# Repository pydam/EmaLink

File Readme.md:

# EmaLink

A device that bridges the communication between Loop software application and Omnipod and Medtronic insulin pumps. This is a fork from RileyLink, focusing on reducing size of the device, improving communication range and extending battery life. Also, you can charge EmaLink with any micro USB charger - much broader available vs. the mini port USB used by RileyLink.

### Turning on
Use a nail, a small plastic or a wood bit to move the power switch towards the USB port. When EmaLink is powered on, you should see a red and a green LED turning on for 1 second.

### Connecting EmaLink to Loop/FreeAPS/AndroidAPS
Please follow the instructions provided by each application for connecting to EmaLink, the procedure is the same as for RileyLink, just the name of the device will be EmaLink.Once EmaLink is connected to Loop/FreeAPS/AndroidAPS, a green led will start blinking every 3 seconds on EmaLink.

### Charging

Once the battery gets almost depleted, a red led will start blinking every 3 seconds.
To charge it, you can use any micro USB charger from a phone, tablet, headset or another device. You can even use a power bank to charge it if it has a micro USB cable. Charging is considered finished after the red led (the one close to the USB connector) is turned off. It may take up to 3 hours for Nano.
For QI versions, charging can be also done with any QI compatible charge. Place EmaLink with the coil (you can see a round, copper coil, through the case) down on the middle of the QI charger and check that a red led is lighting from the top of the EmaLink. Once charging is completed, you should remove EmaLink from the charger as the charger reduces communication range.
Charging can be done every few days until EmaLink is fully charged (the red led turned off) or for a few minutes every day, depending on your schedule. Overnight charging also works well with a Micro USB charge but avoid leaving QI versions on the QI charger overnight as this reduced communication range and may generate red loops.

### LED Lights 

There are 3 leds on the back of the device: a red one, close to the micro USB charging port, and a red + green cluster on the other side. First, turn the EmaLink on by flipping the switch located next to the micro USB port. After you switch-on EmaLink, the red + green cluster will light-up for 1 second. When you connect EmaLink to AAPS on Loop over bluetooth, the green led will start blinking every 3 seconds. The green led will stop blinking once battery is almost depleted. The red led will start blinking once battery is almost depleted, you should consider charging it in the next few hours.

### Case

I have designed a new case to be 3D printed with TPU material. TPU is a flexbile material that cannot be shattered, this makes EmaLink
drop proof. There are several case styles to chose from, pick the one that makes most sense for your needs.

### Hardware

See the [hardware](https://github.com/sks01/emalink/tree/master/hardware) directory for design files to build it. The hardware design is released under [Creative Commons Share-alike 3.0](http://creativecommons.org/licenses/by-sa/3.0/).  

### Firmware

The code in the [firmware](https://github.com/sks01/emalink/tree/master/firmware) directory runs on the hardware.  There are two main chips and thus two firmware images.
Check the "EmaLink 3_7 3_8 - firmware update guide.docx" if you would like to understand how you can update the firmware for EmaLink with PCB version 3.7, 3.8 or 3.9.

Check the "EmaLink 3_2 3_3 - firmware update guide.docx" if you would like to understand how you can update the firmware for EmaLink with PCB version 3.2 or 3.3. You can use breadboard wires also but you may need to keep them at an angle while flashing as the PCB holes are slightly bigger.

Check the "EmaLink%204_4%20-%20firmware%20update%20guide.pdf" if you would like to understand how you can update the firmware for EmaLink with PCB version 4.x. 

### License

The MIT License (MIT)

Copyright (c) 2015 Pete Schwamb

Permission is hereby granted, free of charge, to any person obtaining a copy
of this software and associated documentation files (the "Software"), to deal
in the Software without restriction, including without limitation the rights
to use, copy, modify, merge, publish, distribute, sublicense, and/or sell
copies of the Software, and to permit persons to whom the Software is
furnished to do so, subject to the following conditions:

The above copyright notice and this permission notice shall be included in all
copies or substantial portions of the Software.

THE SOFTWARE IS PROVIDED "AS IS", WITHOUT WARRANTY OF ANY KIND, EXPRESS OR
IMPLIED, INCLUDING BUT NOT LIMITED TO THE WARRANTIES OF MERCHANTABILITY,
FITNESS FOR A PARTICULAR PURPOSE AND NONINFRINGEMENT. IN NO EVENT SHALL THE
AUTHORS OR COPYRIGHT HOLDERS BE LIABLE FOR ANY CLAIM, DAMAGES OR OTHER
LIABILITY, WHETHER IN AN ACTION OF CONTRACT, TORT OR OTHERWISE, ARISING FROM,
OUT OF OR IN CONNECTION WITH THE SOFTWARE OR THE USE OR OTHER DEALINGS IN THE
SOFTWARE.

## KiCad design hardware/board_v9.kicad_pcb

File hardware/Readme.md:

# EmaLink Hardware

 *  Project_EL v4.3_2021-04-12_19-27-16.zip - EasyEDA project for version 4.3
 *  Schematic_EL v4.x.pdf - Schematic for versions 4.1-4.2
 *  Project_EL v4.1.zip - EasyEDA project for versions 4.1-4.2
 *  Gerber_EL v4.2 PCB.zip - Gerber files for version 4.2
 
### PCB Assembly

You will have to look at the schematic and the board design in Kicad to know where the parts go, and how they are oriented.

I use a hot-air rework station to solder the BLE113 module, the CC1110 chip, the USB connector, the 24Mhz crystal and the 3 power coils. The rest can be soldered with normal soldering station but require good soldering skills (especially the balun and the RF tuning network)

### License

The hardware design is released under [Creative Commons Share-alike 3.0](http://creativecommons.org/licenses/by-sa/3.0/).

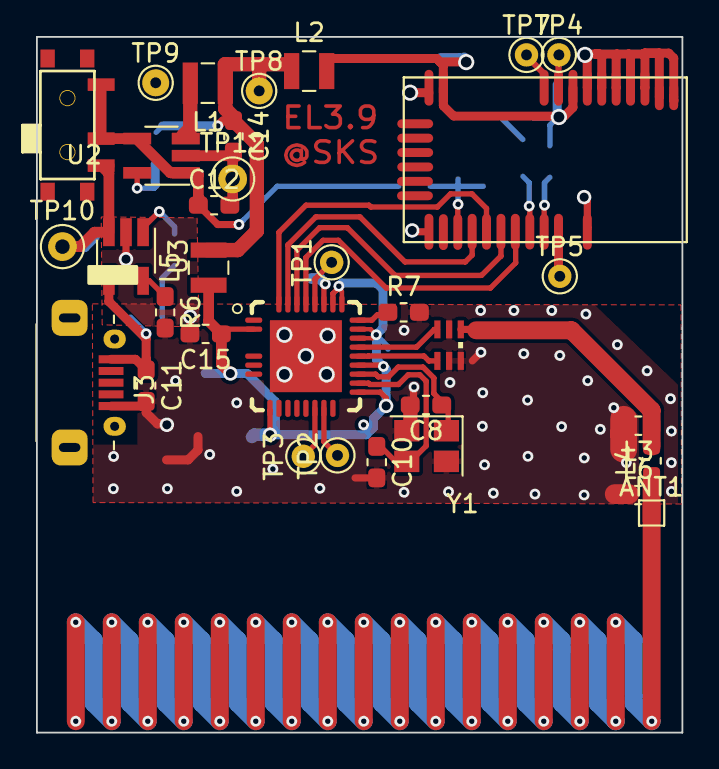
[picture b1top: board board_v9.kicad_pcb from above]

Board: 2 copper layers, 35.9 x 38.6 mm, 52 parts (0 on the bottom side), 34 nets.

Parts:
ANT1: ANTENNA; TestPoint_Pad_1.0x1.0mm
C1, C2, C5, C6, C9, C15, C16: 1uF; C_0603_1608Metric_Pad1.05x0.95mm_HandSolder
C3, C4, C12, C14: 10uF; C_0603_1608Metric_Pad1.05x0.95mm_HandSolder
C7, C11, C13: 4.7uF; C_0603_1608Metric_Pad1.05x0.95mm_HandSolder
C8, C10: 12pF ±5%; C_0603_1608Metric_Pad1.05x0.95mm_HandSolder
CC1: CC1110; QLP-36_CC1110
D3: ORANGE; LED_0603_1608Metric_Pad1.05x0.95mm_HandSolder
D4: RED; LED_0603_1608Metric_Pad1.05x0.95mm_HandSolder
D5: GREEN; LED_0603_1608Metric_Pad1.05x0.95mm_HandSolder
IC1: 0433BM15A0001
J3: USB_B_Micro; U254-051T-4BH23-S2B
L1, L2, L5: 1.5u uH; L_Wuerth_MAPI-2512
L3: 6.8nH; L_0603_1608Metric
L4, L6: 12nH; L_0603_1608Metric
R5: 470; C_0603_1608Metric_Pad1.05x0.95mm_HandSolder
R6: 8.06k; C_0603_1608Metric_Pad1.05x0.95mm_HandSolder
R7: 56kOhm ± 1%; C_0603_1608Metric_Pad1.05x0.95mm_HandSolder
R8, R11: 249k; C_0603_1608Metric_Pad1.05x0.95mm_HandSolder
R9: 100; C_0603_1608Metric_Pad1.05x0.95mm_HandSolder
R12: 82k; C_0603_1608Metric_Pad1.05x0.95mm_HandSolder
R13: 100k; C_0603_1608Metric_Pad1.05x0.95mm_HandSolder
SW1: SW_SPDT; SLIDE_SWITCH_SMD
TP1: RES_CC; TestPoint_THTPad_D1.5mm_Drill0.7mm
TP2: DC_CC; TestPoint_THTPad_D1.5mm_Drill0.7mm
TP3: DD_CC; TestPoint_THTPad_D1.5mm_Drill0.7mm
TP4: DC_BLE; TestPoint_THTPad_D1.5mm_Drill0.6mm
TP5: RES_BLE; TestPoint_THTPad_D1.5mm_Drill0.6mm
TP7: DD_BLE; TestPoint_THTPad_D1.5mm_Drill0.6mm
TP8: VDD; TestPoint_THTPad_D1.5mm_Drill0.6mm
TP9: GND; TestPoint_THTPad_D1.5mm_Drill0.6mm
TP10: Vbat; TestPoint_THTPad_D2.0mm_Drill1.0mm
TP12: GND; TestPoint_THTPad_D2.0mm_Drill1.0mm
U1: BLE113-A
U2: XI AN Aerosemi M3406; SOT-23-5_HandSoldering
U3: XT4052; SOT-23-5_HandSoldering
Y1: 24Mhz; Crystal_SMD_3225-4Pin_3.2x2.5mm

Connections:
BLE_VBAT: C7.1, R11.1, R13.2, U1.P0_6
GND: C1.2, C2.2, C3.2, C4.2, C5.2, C6.2, C7.2, C8.2, C9.1, C10.2, C11.2, C12.2, C13.2, C14.2, C15.2, C16.2, CC1.37, IC1.2, IC1.5, IC1.6, J3.5, L3.2, L6.1, R6.2, R7.2, R12.1, R13.1, TP9.1, TP12.1, U1.GND, U1.GND@2, U1.GND@3, U1.GND@4, U1.GND@5, U1.GND@6, U1.GND@7, U1.GND@8, U1.GND@9, U1.GND@10, U2.2, U3.2, Y1.2, Y1.4
LED1_OUT: D5.2, U1.P0_0
LED2_OUT: R9.1, U1.P0_1
unnamed: ANT1.1, L4.1, L6.2
unnamed: C1.1, C2.1, C4.1, C6.1, C15.1, C16.1, CC1.2, CC1.10, CC1.19, CC1.22, CC1.25, CC1.26, CC1.28, CC1.29, L5.1
unnamed: C3.1, C5.1, D4.1, D5.1, L2.2, U1.AVDD, U1.DVDD
unnamed: C8.1, CC1.21, Y1.1
unnamed: C9.2, CC1.30
unnamed: C10.1, CC1.20, Y1.3
unnamed: CC1.15, TP3.1
unnamed: CC1.16, TP2.1
unnamed: CC1.23, IC1.4
unnamed: CC1.24, IC1.3
unnamed: CC1.27, R7.1
unnamed: CC1.31, TP1.1
unnamed: CC1.32, U1.P0_2
unnamed: CC1.33, U1.P0_3
unnamed: CC1.34, U1.P0_5
unnamed: CC1.35, U1.P0_4
unnamed: D3.2, R5.1
unnamed: D4.2, R9.2
unnamed: IC1.1, L3.1, L4.2
unnamed: L1.2, U2.3
unnamed: R5.2, U3.1
unnamed: R6.1, U3.5
unnamed: R8.1, R12.2, U2.5
unnamed: TP4.1, U1.P2_2
unnamed: TP5.1, U1.RESET
unnamed: TP7.1, U1.P2_1
USB_5V: C11.1, D3.1, J3.1, U3.4
V+: C12.1, R11.2, SW1.1, SW1.2, U2.1, U2.4
VBAT: C13.1, SW1.3, TP10.1, U3.3
VDD: C14.1, L1.1, L2.1, L5.2, R8.2, TP8.1

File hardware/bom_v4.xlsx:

Qty | Reference(s) | Value | Footprint
1 | ANT1 | ANTENNA | footprints:W3127 433Mhz
7 | C1, C2, C5, C6, C9, C15, C16 | 1uF | Capacitor_SMD:C_0603_1608Metric_Pad1.05x0.95mm_HandSolder
4 | C3, C4, C12, C14 | 10uF | Capacitor_SMD:C_0603_1608Metric_Pad1.05x0.95mm_HandSolder
3 | C7, C11, C13 | 4.7uF | Capacitor_SMD:C_0603_1608Metric_Pad1.05x0.95mm_HandSolder
2 | C8, C10 | 12pF | Capacitor_SMD:C_0603_1608Metric_Pad1.05x0.95mm_HandSolder
1 | CC1 | CC1110 | footprints:QLP-36_CC1110
1 | D3 | ORANGE | LED_SMD:LED_0603_1608Metric_Pad1.05x0.95mm_HandSolder
1 | D4 | RED | LED_SMD:LED_0603_1608Metric_Pad1.05x0.95mm_HandSolder
1 | D5 | GREEN | LED_SMD:LED_0603_1608Metric_Pad1.05x0.95mm_HandSolder
1 | IC1 | 0433BM15A0001 | footprints:0433BM15A0001
1 | J3 | USB_B_Micro | footprints:U254-051T-4BH23-S2B
3 | L1, L2, L5 | 1.5u uH | Inductor_SMD:L_Wuerth_MAPI-2512
1 | L3 | 6.8nH | Inductor_SMD:L_0402_1005Metric
1 | L4 | 12nH | Inductor_SMD:L_0402_1005Metric
1 | R5 | 470Ohm | Capacitor_SMD:C_0603_1608Metric_Pad1.05x0.95mm_HandSolder
1 | R6 | 8.06k | Capacitor_SMD:C_0603_1608Metric_Pad1.05x0.95mm_HandSolder
1 | R7 | 56kOhm | Capacitor_SMD:C_0603_1608Metric_Pad1.05x0.95mm_HandSolder
2 | R8, R11 | 249k | Capacitor_SMD:C_0603_1608Metric_Pad1.05x0.95mm_HandSolder
1 | R9 | 100Ohm | Capacitor_SMD:C_0603_1608Metric_Pad1.05x0.95mm_HandSolder
1 | R10 | 0Ohm | Capacitor_SMD:C_0603_1608Metric_Pad1.05x0.95mm_HandSolder
1 | R12 | 82k | Capacitor_SMD:C_0603_1608Metric_Pad1.05x0.95mm_HandSolder
1 | R13 | 100k | Capacitor_SMD:C_0603_1608Metric_Pad1.05x0.95mm_HandSolder
1 | SW1 | SW_SPDT | footprints:SLIDE_SWITCH_SMD
1 | U1 | BLE113-A | footprints:BLE113-A
1 | U2 | XI AN Aerosemi M3406 | Package_TO_SOT_SMD:SOT-23-5_HandSoldering
1 | U3 | XT4052 | Package_TO_SOT_SMD:SOT-23-5
1 | Y1 | 24Mhz | Crystal:Crystal_SMD_3225-4Pin_3.2x2.5mm

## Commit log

2020-02-03 PCB version 3.2
2020-02-03 Version 3.2 updates
2020-02-03 Updated pictures
2020-02-03 Updated pictures links
2020-02-03 Updates to reflect 3.2 changes
2020-02-03 Updated PCB
2020-02-03 Updated BLE firmware version log
2020-02-03 Rename spi1_alt2_RILEYLINK_US_STDLOC.hex to cc1110_emalink_2.2.hex
2020-02-03 Rename spi1_alt2_RILEYLINK_US_STDLOC.hex to cc1110_emalink_3.5.hex
2020-02-16 Added BOM
2020-07-29 Updated to version 3.7
2020-07-29 Updated to version 2.12
2020-07-29 updated CC firmware to 2.12
2020-07-29 Updated for new PCB versions 3.7 and 3.8
2020-07-29 Added schematic and PCB version 3.7
2020-07-29 New EmaLink versions added
2020-08-02 Added Maxx
2020-08-02 Added Classic 3.7
2020-08-02 Added NeoClassic
2020-08-02 Update PCB pictures
2020-08-02 Added XXS
2020-08-16 Added firmware update document
2020-08-16 Added firmware update guide for 3.2 and 3.3 PCBs
2020-08-17 Added XS pictures
2020-08-17 Added Medium case pictures
2020-08-17 Added Classic 3.2 case pictures
2020-09-13 Added instructions for solving soldering issues with CC1110 chip
2020-09-13 Added CC1110 re-soldering guide in PDF format
2020-09-18 Added 3.12 firmware for Omnipod users
    Use this firmware if you have communication issues (red loops) with Loop/FreeAPS and you currently have 2.12 firmware
2020-10-06 Added CC1110_2.2.16
    Fixed a bug that would lost ~25% of long packets sent by Omnipod to EmaLink
2020-10-25 Added 3XS picture
2020-10-26 Added PCB version 3.9
2020-10-27 Updated Tinkercad links
2020-12-04 Add "reduce noise floor" instructions
2020-12-18 Add Battery Level reporting in Loop or FreeAps
2020-12-26 Added Capture Loop debug information with Xcode
2021-01-19 Added CC firmware 2.2.19
    Corrected bolus errors for Loop Medtronic users when using a Pump with MySentry feature
2021-01-19 EmaLink Power-on video
2021-01-31 Updated for version 4.2
2021-02-05 Added files for PCB v3.9
2021-02-14 Added Nano
2021-02-14 Updated Nano
2021-02-16 Updated to version 3.11
2021-02-21 Added Nano PCB pictures
2021-03-03 Added firmware update guide for PCB v5.0 (Nano)
2021-03-04 Added pictures for Large version
2021-04-12 Add EmaLink v4.3 EasyEDA Project
2021-04-23 Added CC1110 2.2.21 firmware
2021-04-23 Added BLE113 v3.13 firmware
2021-04-23 Added BLE v3.11 firmware
2021-04-23 Described the battery map calibration procedure
2021-06-21 Added BLE v3.15
2021-06-21 Added CC1110 v2.2.22
2021-07-10 Added BLE v3.17
2021-07-28 Added custom BLE firmware for RileyLink
2021-07-28 Added custom CC1110 firmware for RileyLink
2021-07-28 RileyLink customization
2021-09-29 battery level indicator patch for Loop v2.2.6
2021-10-25 Added firmware v3.18 for BLE113
2021-10-25 Added CC1110 firmware v2.2.23
